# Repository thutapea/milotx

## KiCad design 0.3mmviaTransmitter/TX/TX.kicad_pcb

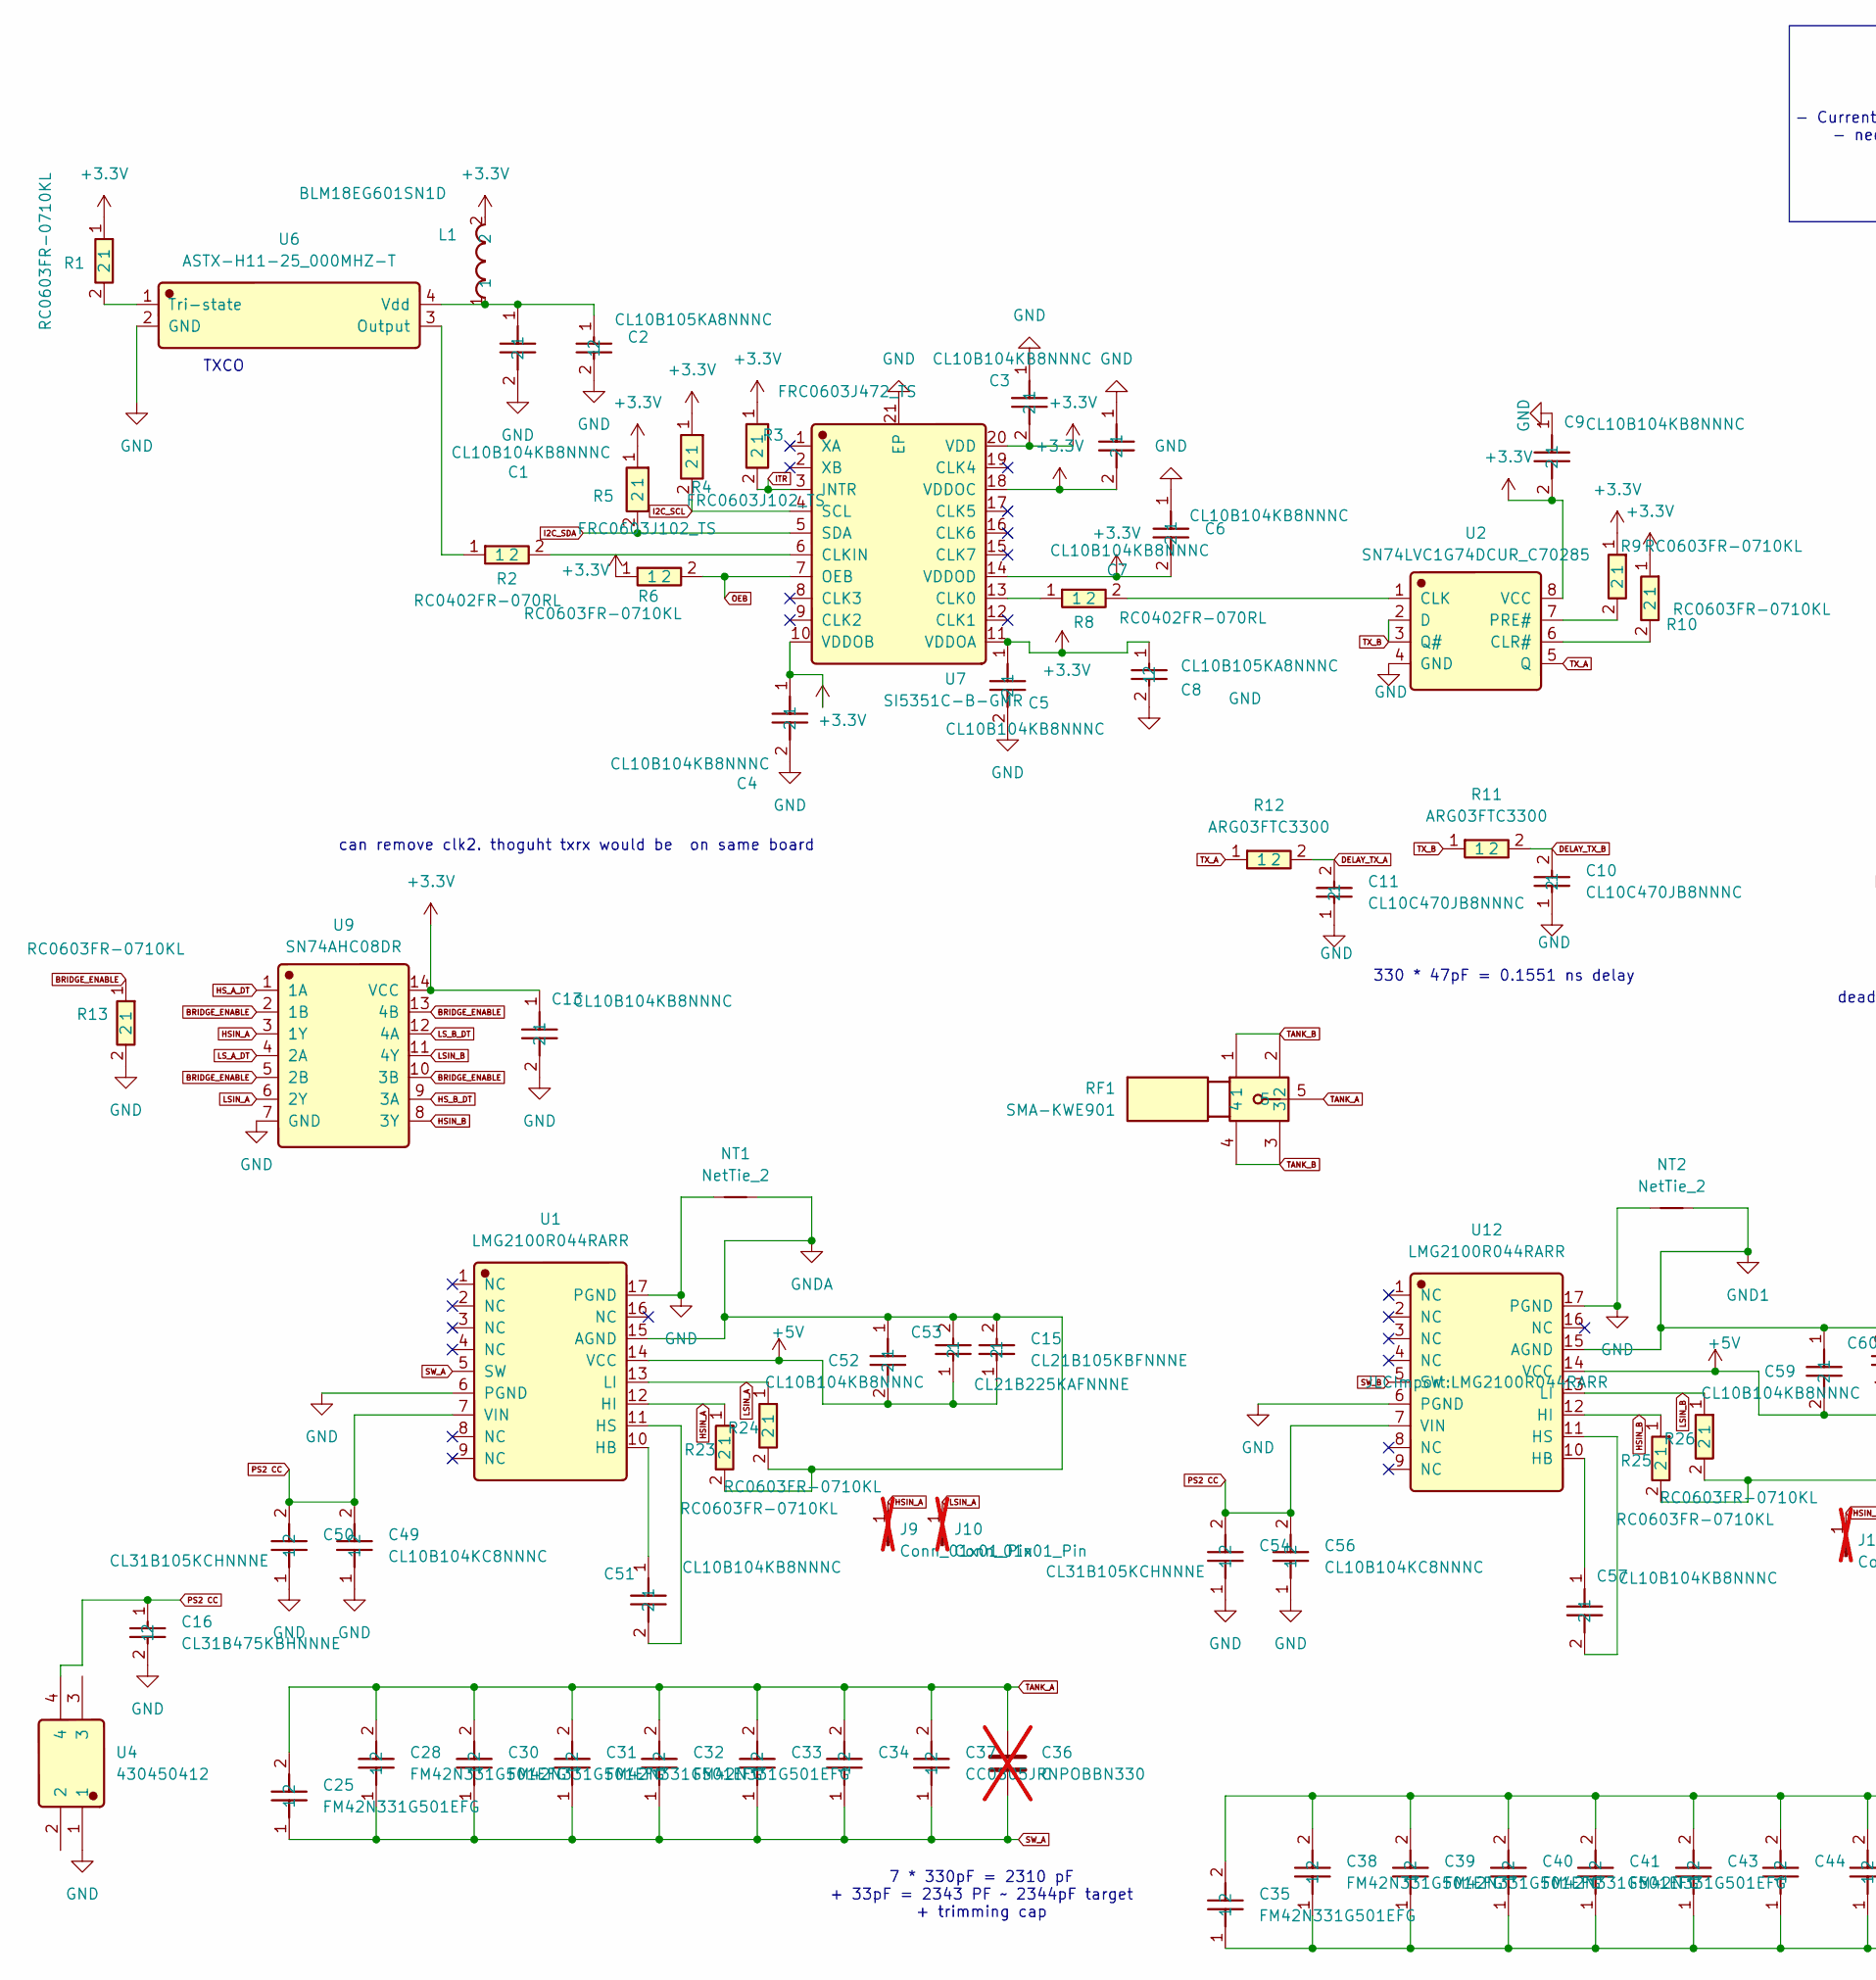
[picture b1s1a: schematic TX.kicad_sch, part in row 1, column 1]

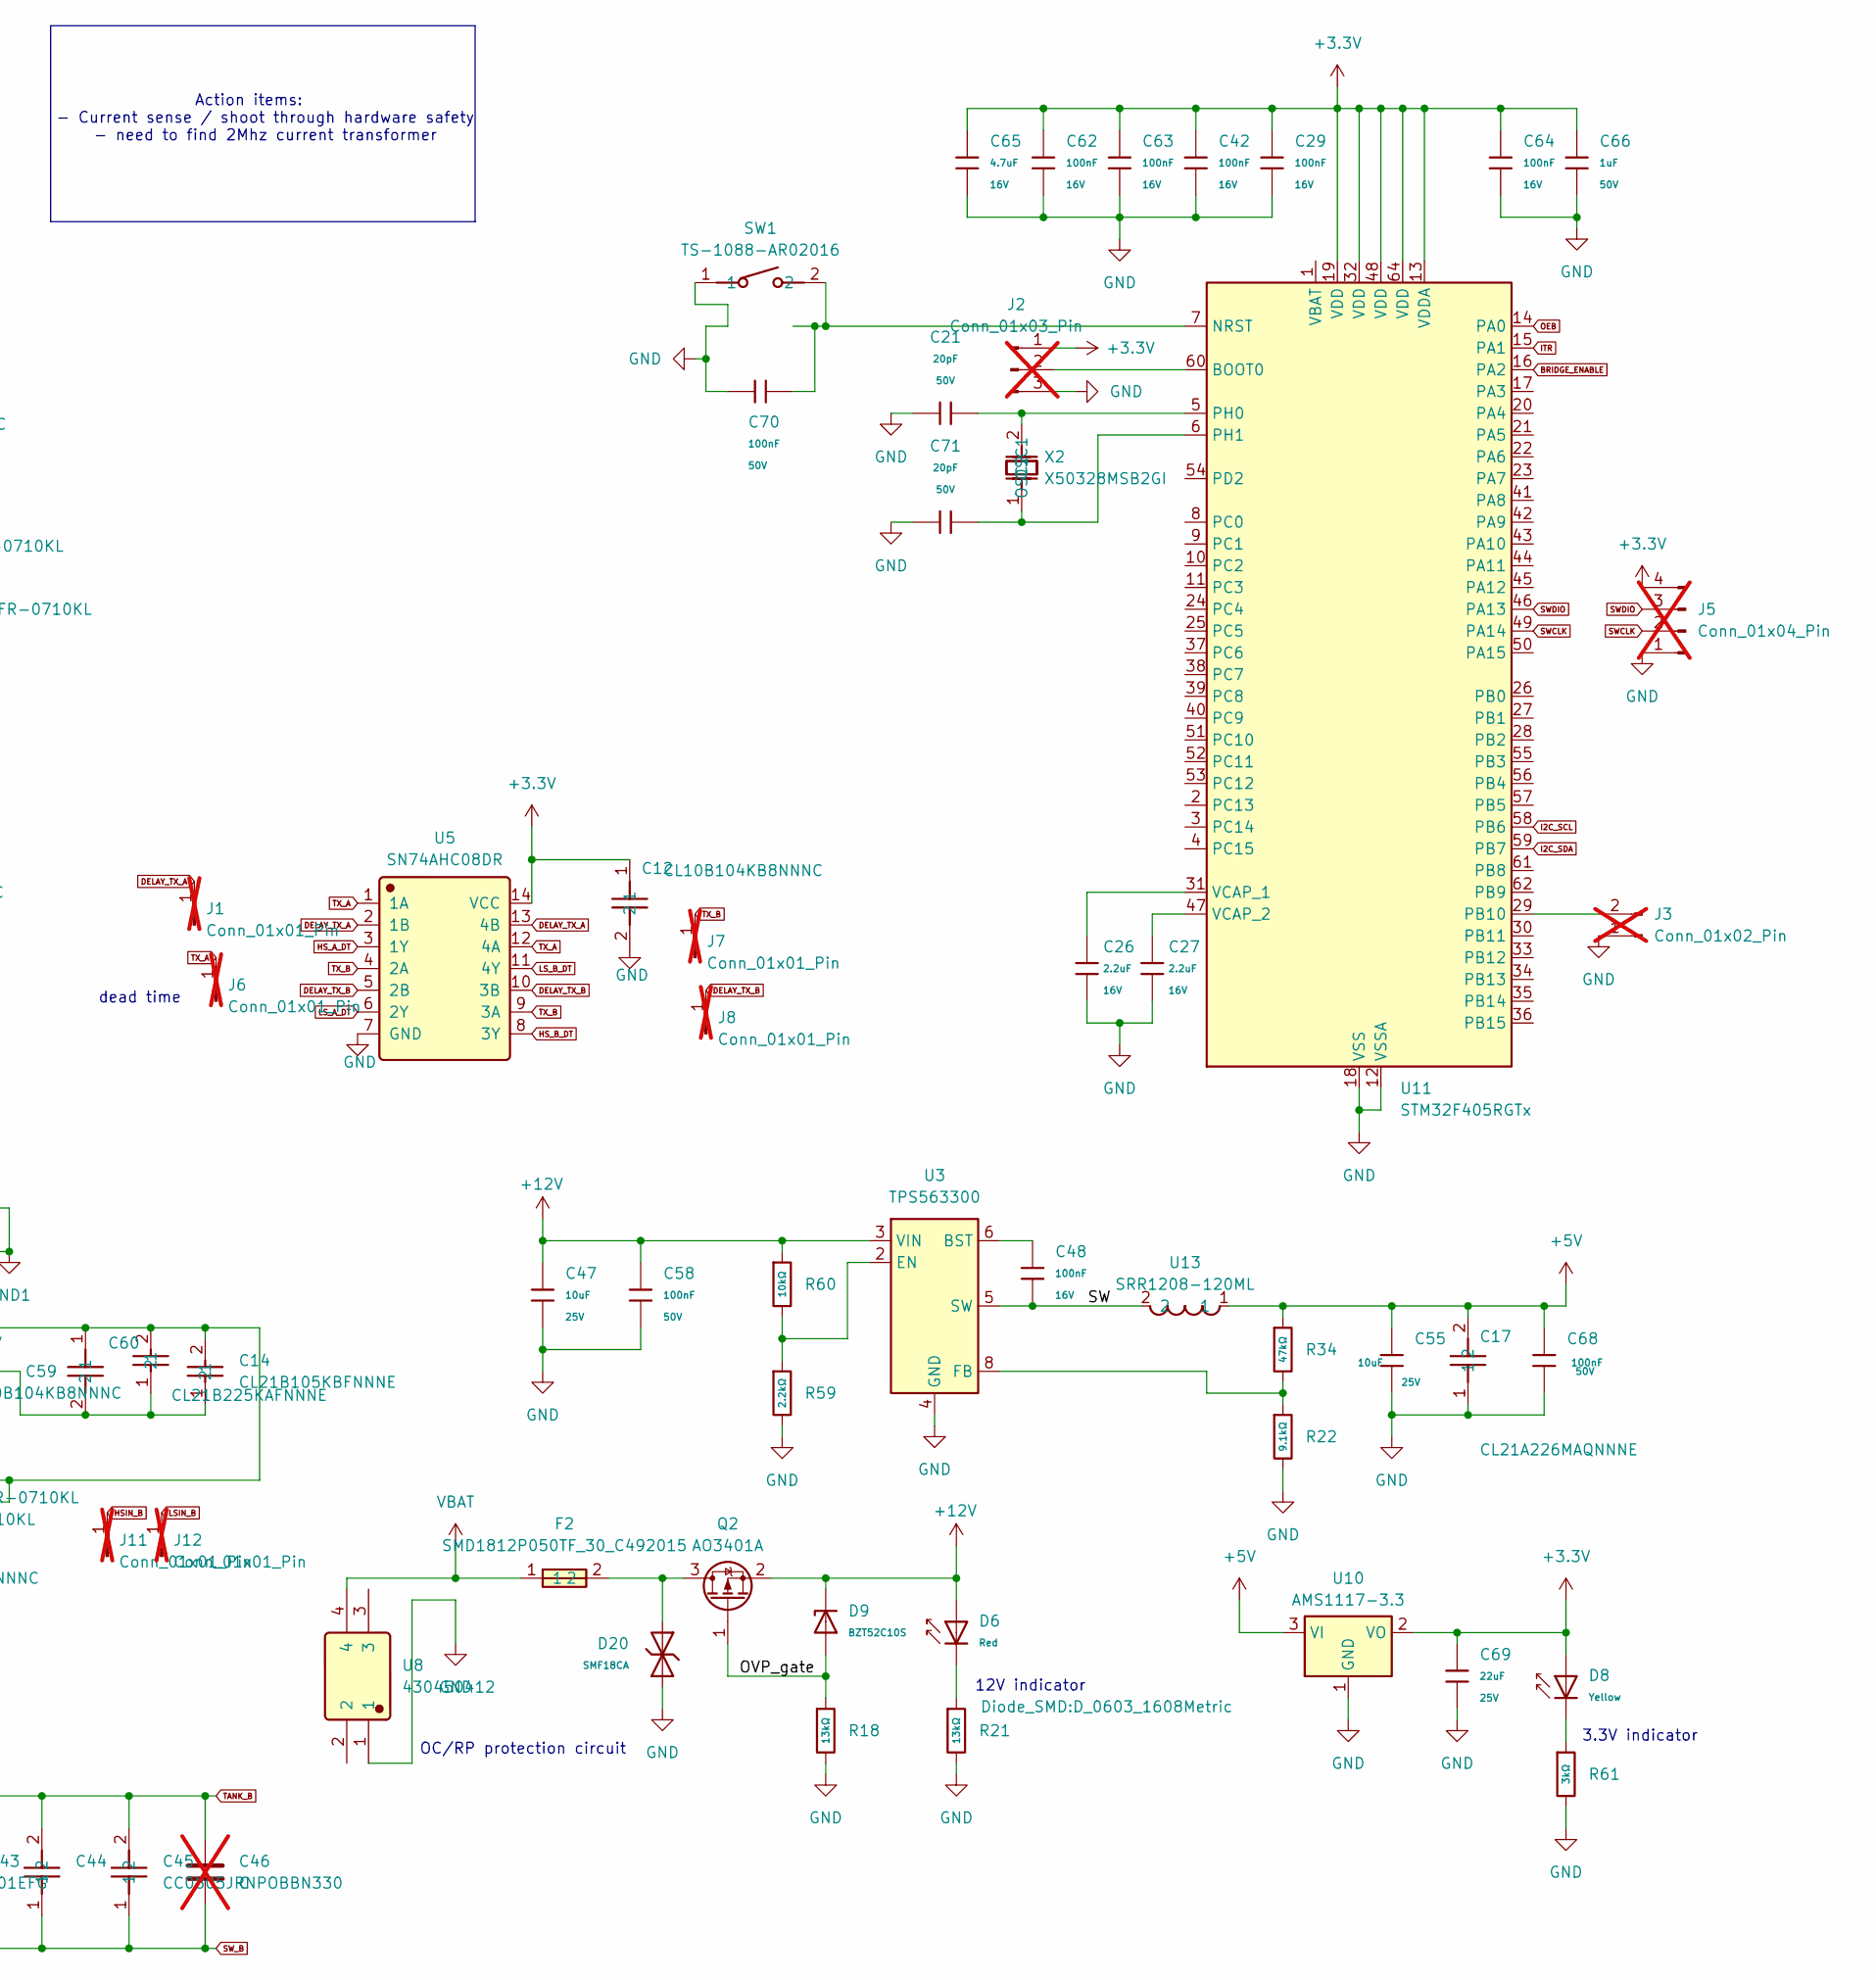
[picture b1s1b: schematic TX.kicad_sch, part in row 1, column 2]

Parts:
C1, C3, C4, C5, C6, C7, C9, C12, C13, C51, C52, C57, C59: CL10B104KB8NNNC; C_0603_1608Metric; Manufacturer Part CL10B104KB8NNNC; LCSC C1591
C2, C8: CL10B105KA8NNNC; C_0603_1608Metric; Manufacturer Part CL10B105KA8NNNC; LCSC C29936
C10, C11: CL10C470JB8NNNC; C_0603_1608Metric; Manufacturer Part CL10C470JB8NNNC; LCSC C1671
C14, C15: CL21B105KBFNNNE; C_0805_2012Metric; Manufacturer Part CL21B105KBFNNNE; LCSC C28323
C16: CL31B475KBHNNNE; C_1206_3216Metric; Manufacturer Part CL31B475KBHNNNE; LCSC C51205
C17: CL21A226MAQNNNE; C_0805_2012Metric; Manufacturer Part CL21A226MAQNNNE; LCSC C45783
C21, C71: 20pF; C_0402_1005Metric; Voltage Rated 50V; Tolerance ±5%; Part 0402CG200J500NT; LCSC C1554
C25, C28, C30, C31, C32, C33, C34, C35, C38, C39, C40, C41, C43, C44: FM42N331G501EFG; C_1808_4520Metric; Manufacturer Part FM42N331G501EFG; LCSC C22376361
C26, C27: 2.2uF; C_0603_1608Metric; Voltage Rated 16V; Tolerance ±10%; Part CL10A225KO8NNNC; LCSC C23630
C29, C42, C48, C62, C63, C64: 100nF; C_0402_1005Metric; Voltage Rated 16V; Tolerance ±10%; Part CL05B104KO5NNNC; LCSC C1525
C36, C46: C; C_0603_1608Metric; not fitted
C37, C45: CC0805JRNPOBBN330; C_0805_2012Metric; Manufacturer Part CC0805JRNPOBBN330; LCSC C113838
C47, C55: 10uF; C_0603_1608Metric; Voltage Rated 25V; Tolerance ±20%; Part CL10A106MA8NRNC; LCSC C96446
C49, C56: CL10B104KC8NNNC; C_0603_1608Metric; Manufacturer Part CL10B104KC8NNNC; LCSC C15725
C50, C54: CL31B105KCHNNNE; C_1206_3216Metric; Manufacturer Part CL31B105KCHNNNE; LCSC C13832
C53, C60: CL21B225KAFNNNE; C_0805_2012Metric; Manufacturer Part CL21B225KAFNNNE; LCSC C19110
C58, C68, C70: 100nF; C_0603_1608Metric; Voltage Rated 50V; Tolerance ±10%; Part CC0603KRX7R9BB104; LCSC C14663
C65: 4.7uF; C_0603_1608Metric; Voltage Rated 16V; Tolerance ±10%; Part CL10A475KO8NNNC; LCSC C19666
C66: 1uF; C_0603_1608Metric; Voltage Rated 50V; Tolerance ±10%; Part CL10A105KB8NNNC; LCSC C15849
C69: 22uF; C_0805_2012Metric; Voltage Rated 25V; Tolerance ±20%; Part CL21A226MAQNNNE; LCSC C45783
D6: Red; D_0603_1608Metric; Part KT-0603R; LCSC C2286
D8: Yellow; D_0603_1608Metric; Forward Voltage (VF) 1.6V~2.6V; Part NCD0603Y2; LCSC C89811
D9: BZT52C10S; D_SOD-323; Part BZT52C10S; LCSC C19077446
D20: SMF18CA; D_SOD-123F; Breakdown Voltage 20V; Part SMF18CA; LCSC C19077513
F2: SMD1812P050TF_30_C492015; Manufacturer Part SMD1812P050TF/30; LCSC C492015
J1, J6, J7, J8, J9, J10, J11, J12: Conn_01x01_Pin; PinHeader_1x01_P2.54mm_Vertical; not fitted
J2: Conn_01x03_Pin; PinSocket_1x03_P2.54mm_Vertical; not fitted
J3: Conn_01x02_Pin; PinHeader_1x02_P2.54mm_Vertical; not fitted
J5: Conn_01x04_Pin; PinHeader_1x04_P2.54mm_Vertical; not fitted
L1: BLM18EG601SN1D; L_0603_1608Metric; Manufacturer Part BLM18EG601SN1D; LCSC C20345
NT1, NT2: NetTie_2; NetTie-2_SMD_Pad2.0mm
Q2: AO3401A; SOT-23
R1, R6, R9, R10, R13, R23, R24, R25, R26: RC0603FR-0710KL; R_0603_1608Metric; Manufacturer Part RC0603FR-0710KL; LCSC C98220
R2, R8: RC0402FR-070RL; R_0402_1005Metric; Manufacturer Part RC0402FR-070RL; LCSC C106231
R3: FRC0603J472_TS; R_0603_1608Metric; Manufacturer Part FRC0603J472 TS; LCSC C2907166
R4, R5: FRC0603J102_TS; R_0603_1608Metric; Manufacturer Part FRC0603J102 TS; LCSC C2907113
R11, R12: ARG03FTC3300; R_0603_1608Metric; Manufacturer Part ARG03FTC3300; LCSC C217969
R18, R21: 13kΩ; R_0603_1608Metric; Overload Voltage (Max) 75V; Tolerance ±1%; Part 0603WAF1302T5E; LCSC C22797
R22: 9.1kΩ; R_0603_1608Metric; Overload Voltage (Max) 75V; Tolerance ±1%; Part 0603WAF9101T5E; LCSC C23260
R34: 47kΩ; R_0402_1005Metric; Overload Voltage (Max) 50V; Tolerance ±1%; Part 0402WGF4702TCE; LCSC C25792
R59: 2.2kΩ; R_0402_1005Metric; Overload Voltage (Max) 50V; Tolerance ±1%; Part 0402WGF2201TCE; LCSC C25879
R60: 10kΩ; R_0402_1005Metric; Overload Voltage (Max) 50V; Tolerance ±1%; Part 0402WGF1002TCE; LCSC C25744
R61: 3kΩ; R_0603_1608Metric; Overload Voltage (Max) 75V; Tolerance ±1%; Part 0603WAF3001T5E; LCSC C4211
RF1: SMA-KWE901; Manufacturer Part SMA-KWE901; LCSC C914553
SW1: TS-1088-AR02016; SW_PUSH_1P1T_6x3.5mm_H5.0_APEM_MJTP1250; Manufacturer Part TS-1088-AR02016; LCSC C54141293
U1, U12: LMG2100R044RARR; Manufacturer Part LMG2100R044RARR; LCSC C22453052
U2: SN74LVC1G74DCUR_C70285; VSSOP-8_2.3x2mm_P0.5mm; Manufacturer Part SN74LVC1G74DCUR; LCSC C70285
U3: TPS563300; SOT-583-8
U4, U8: 430450412; Molex_Micro-Fit_3.0_43045-0412_2x02_P3.00mm_Vertical; Manufacturer Part 430450412; LCSC C277721
U5, U9: SN74AHC08DR; SOIC-14_3.9x8.7mm_P1.27mm; Manufacturer Part SN74AHC08DR; LCSC C6937
U6: ASTX-H11-25_000MHZ-T; Crystal_SMD_3225-4Pin_3.2x2.5mm; Manufacturer Part ASTX-H11-25.000MHZ-T; LCSC C7217716
U7: SI5351C-B-GMR; Manufacturer Part SI5351C-B-GMR; LCSC C2649375
U10: AMS1117-3.3; SOT-223-3_TabPin2
U11: STM32F405RGTx; LQFP-64_10x10mm_P0.5mm; LCSC C15742
U13: SRR1208-120ML; Manufacturer Part SRR1208-120ML; LCSC C1329356
X2: X50328MSB2GI; Crystal_SMD_5032-2Pin_5.0x3.2mm; Manufacturer Part X50328MSB2GI; LCSC C115962

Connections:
+3.3V: C3.2, C4.1, C5.1, C6.2, C7.2, C8.1, C9.2, C12.1, C13.1, C29.1, C42.1, C62.1, C63.1, C64.1, C65.1, C66.1, C69.1, D8.2, J2.1, J5.4, L1.2, R1.1, R3.1, R4.1, R5.1, R6.1, R9.1, R10.1, U2.8 (VCC), U5.14 (VCC), U7.10 (VDDOB), U7.11 (VDDOA), U7.14 (VDDOD), U7.18 (VDDOC), U7.20 (VDD), U9.14 (VCC), U10.2 (VO), U11.13 (VDDA), U11.19 (VDD), U11.32 (VDD), U11.48 (VDD), U11.64 (VDD); also elsewhere on the board
+5V: C14.1, C15.1, C17.2, C52.2, C53.1, C55.1, C59.2, C60.1, C68.1, R34.1, U1.14 (VCC), U10.3 (VI), U12.14 (VCC), U13.1
+12V: C47.1, C58.1, D6.2, D9.1, Q2.2 (S), R60.1, U3.3 (VIN); also elsewhere on the board
/OVP_gate: D9.2, Q2.1 (G), R18.1
/SW: C48.2, U3.5 (SW), U13.2
BRIDGE_ENABLE: R13.1, U9.2 (1B), U9.5 (2B), U9.10 (3B), U9.13 (4B), U11.16 (PA2)
DELAY_TX_A: C11.2, J1.1 (Pin_1_1), R12.2, U5.2 (1B), U5.13 (4B)
DELAY_TX_B: C10.2, J8.1 (Pin_1_1), R11.2, U5.5 (2B), U5.10 (3B)
GND: C1.2, C2.2, C3.1, C4.2, C5.2, C6.1, C7.1, C8.2, C9.1, C10.1, C11.1, C12.2, C13.2, C16.2, C17.1, C21.1, C26.2, C27.2, C29.2, C42.2, C47.2, C49.1, C50.1, C54.1, C55.2, C56.1, C58.2, C62.2, C63.2, C64.2, C65.2, C66.2, C68.2, C69.2, C70.2, C71.1, D20.1, J2.3, J3.1, J5.1, NT1.1, NT2.1, R13.2, R18.2, R21.2, R22.2, R59.2, R61.2, SW1.1, U1.6 (PGND), U1.17 (PGND), U2.4 (GND), U3.4 (GND), U4.1, U5.7 (GND), U6.2 (GND), U7.21 (EP), U8.1, U9.7 (GND), U10.1 (GND), U11.12 (VSSA), U11.18 (VSS), U11.63 (VSS), U12.6 (PGND), U12.17 (PGND)
GND1: C14.2, C59.1, C60.2, NT2.2, R25.2, R26.2, U12.15 (AGND)
GNDA: C15.2, C52.1, C53.2, NT1.2, R23.2, R24.2, U1.15 (AGND)
HSIN_A: J9.1 (Pin_1_1), R23.1, U1.12 (HI), U9.3 (1Y)
HSIN_B: J11.1 (Pin_1_1), R25.1, U9.8 (3Y), U12.12 (HI)
HS_A_DT: U5.3 (1Y), U9.1 (1A)
HS_B_DT: U5.8 (3Y), U9.9 (3A)
I2C_SCL: R4.2, U7.4 (SCL), U11.58 (PB6)
I2C_SDA: R5.2, U7.5 (SDA), U11.59 (PB7)
ITR: R3.2, U7.3 (INTR), U11.15 (PA1)
LSIN_A: J10.1 (Pin_1_1), R24.1, U1.13 (LI), U9.6 (2Y)
LSIN_B: J12.1 (Pin_1_1), R26.1, U9.11 (4Y), U12.13 (LI)
LS_A_DT: U5.6 (2Y), U9.4 (2A)
LS_B_DT: U5.11 (4Y), U9.12 (4A)
unnamed: D6.1, R21.1
unnamed: D8.1, R61.1
unnamed: J2.2, U11.60 (BOOT0)
unnamed: J3.2, U11.29 (PB10)
unnamed: D20.2, F2.2, Q2.3 (D)
unnamed: C51.1, U1.10 (HB)
unnamed: C51.2, U1.11 (HS)
unnamed: R8.2, U2.1 (CLK)
unnamed: R9.2, U2.6 (CLR#)
unnamed: R10.2, U2.7 (PRE#)
unnamed: C48.1, U3.6 (BST)
unnamed: R59.1, R60.2, U3.2 (EN)
unnamed 34: R22.1, R34.2, U3.8 (FB); also elsewhere on the board
unnamed: R2.1, U6.3 (Output)
unnamed: R1.2, U6.1 (Tri-state)
unnamed: C1.1, C2.1, L1.1, U6.4 (Vdd)
unnamed: R8.1, U7.13 (CLK0)
unnamed: R2.2, U7.6 (CLKIN)
unnamed: C70.1, SW1.2, U11.7 (NRST)
unnamed: C21.2, U11.5 (PH0), X2.2 (OSC2)
unnamed: C71.2, U11.6 (PH1), X2.1 (OSC1)
unnamed: C26.1, U11.31 (VCAP_1)
unnamed: C27.1, U11.47 (VCAP_2)
unnamed: C57.1, U12.10 (HB)
unnamed: C57.2, U12.11 (HS)
OEB: R6.2, U7.7 (OEB), U11.14 (PA0)
PS2 CC: C16.1, C49.2, C50.2, C54.2, C56.2, U1.7 (VIN), U4.4, U12.7 (VIN)
SWCLK: J5.2, U11.49 (PA14)
SWDIO: J5.3, U11.46 (PA13)
SW_A: C25.1, C28.1, C30.1, C31.1, C32.1, C33.1, C34.1, C36.2, C37.1, U1.5 (SW)
SW_B: C35.1, C38.1, C39.1, C40.1, C41.1, C43.1, C44.1, C45.1, C46.2, U12.5 (SW)
TANK_A: C25.2, C28.2, C30.2, C31.2, C32.2, C33.2, C34.2, C36.1, C37.2, RF1.5
TANK_B: C35.2, C38.2, C39.2, C40.2, C41.2, C43.2, C44.2, C45.2, C46.1, RF1.1, RF1.2, RF1.3, RF1.4
TX_A: J6.1 (Pin_1_1), R12.1, U2.5 (Q), U5.1 (1A), U5.12 (4A)
TX_B: J7.1 (Pin_1_1), R11.1, U2.2 (D), U2.3 (Q#), U5.4 (2A), U5.9 (3A)
VBAT: F2.1, U8.4

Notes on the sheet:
TXCO
Action items: - Current sense / shoot through hardware safety - need to find 2Mhz current transformer
7 * 330pF = 2310 pF + 33pF = 2343 PF ~ 2344pF target + trimming cap
330 * 47pF = 0.1551 ns delay
12V indicator
OC/RP protection circuit
dead time
can remove clk2. thoguht txrx would be on same board
3.3V indicator

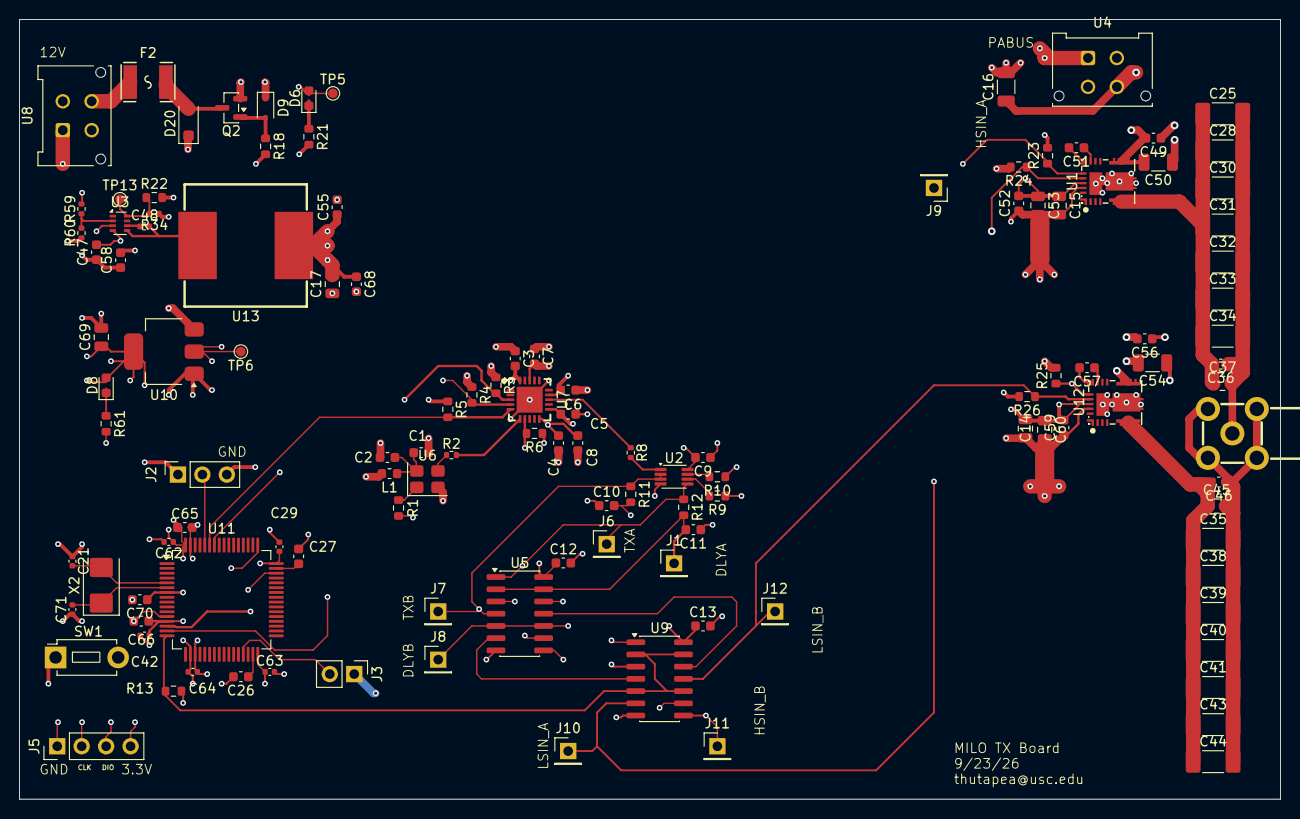
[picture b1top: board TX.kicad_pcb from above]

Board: 6 copper layers, 131.0 x 81.0 mm, 125 parts (0 on the bottom side), 58 nets.

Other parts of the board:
TP5, TP6, TP13: TestPoint_Small; TestPoint_Pad_D1.0mm

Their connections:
+3.3V: TP6.1 (1_1); also elsewhere on the board
+12V: TP5.1 (1_1); also elsewhere on the board
unnamed 34: TP13.1 (1_1); also elsewhere on the board

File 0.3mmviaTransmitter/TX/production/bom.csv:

Designator,Footprint,Quantity,Value,LCSC Part #
"C1, C12, C13, C3, C4, C5, C51, C52, C57, C59, C6, C7, C9",0603,13,CL10B104KB8NNNC,C1591
"C10, C11",0603,2,CL10C470JB8NNNC,C1671
"C14, C15",0805,2,CL21B105KBFNNNE,C28323
C16,1206,1,CL31B475KBHNNNE,C51205
C17,0805,1,CL21A226MAQNNNE,C45783
"C2, C8",0603,2,CL10B105KA8NNNC,C29936
"C21, C71",0402,2,20pF,C1554
"C25, C28, C30, C31, C32, C33, C34, C35, C38, C39, C40, C41, C43, C44",1808,14,FM42N331G501EFG,C22376361
"C26, C27",0603,2,2.2uF,C23630
"C29, C42, C48, C62, C63, C64",0402,6,100nF,C1525
"C37, C45",0805,2,CC0805JRNPOBBN330,C113838
"C47, C55",0603,2,10uF,C96446
"C49, C56",0603,2,CL10B104KC8NNNC,C15725
"C50, C54",1206,2,CL31B105KCHNNNE,C13832
"C53, C60",0805,2,CL21B225KAFNNNE,C19110
"C58, C68, C70",0603,3,100nF,C14663
C65,0603,1,4.7uF,C19666
C66,0603,1,1uF,C15849
C69,0805,1,22uF,C45783
D20,D_SOD-123F,1,SMF18CA,C19077513
D6,0603,1,Red,C2286
D8,0603,1,Yellow,C89811
D9,D_SOD-323,1,BZT52C10S,C19077446
F2,SMD1812P050TF_30_C492015,1,SMD1812P050TF_30_C492015,C492015
L1,0603,1,BLM18EG601SN1D,C20345
Q2,SOT-23,1,AO3401A,
"R1, R10, R13, R23, R24, R25, R26, R6, R9",0603,9,RC0603FR-0710KL,C98220
"R11, R12",0603,2,ARG03FTC3300,C217969
"R18, R21",0603,2,13kΩ,C22797
"R2, R8",0402,2,RC0402FR-070RL,C106231
R22,0603,1,9.1kΩ,C23260
R3,0603,1,FRC0603J472_TS,C2907166
R34,0402,1,47kΩ,C25792
"R4, R5",0603,2,FRC0603J102_TS,C2907113
R59,0402,1,2.2kΩ,C25879
R60,0402,1,10kΩ,C25744
R61,0603,1,3kΩ,C4211
RF1,SMA-KWE901,1,SMA-KWE901,C914553
SW1,SW_PUSH_1P1T_6x3.5mm_H5.0_APEM_MJTP1250,1,TS-1088-AR02016,C54141293
"U1, U12",LMG2100R044RARR,2,LMG2100R044RARR,C22453052
U10,SOT-223-3_TabPin2,1,AMS1117-3.3,
U11,LQFP-64_10x10mm_P0.5mm,1,STM32F405RGTx,C15742
U13,SRR1208-120ML,1,SRR1208-120ML,C1329356
U2,VSSOP-8_2.3x2mm_P0.5mm,1,SN74LVC1G74DCUR_C70285,C70285
U3,SOT-583-8,1,TPS563300,
"U4, U8",Molex_Micro-Fit_3.0_43045-0412_2x02_P3.00mm_Vertical,2,430450412,C277721
"U5, U9",SOIC-14_3.9x8.7mm_P1.27mm,2,SN74AHC08DR,C6937
U6,Crystal_SMD_3225-4Pin_3.2x2.5mm,1,ASTX-H11-25_000MHZ-T,C7217716
U7,SI5351C-B-GMR,1,SI5351C-B-GMR,C2649375
X2,Crystal_SMD_5032-2Pin_5.0x3.2mm,1,X50328MSB2GI,C115962

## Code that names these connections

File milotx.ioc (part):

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Mcu.Name=STM32F405RGTx
Mcu.Package=LQFP64
Mcu.UserName=STM32F405RGTx
PA0-WKUP.Signal=GPIO_Output
PA13.Mode=Serial_Wire
PA13.Signal=SYS_JTMS-SWDIO
PA14.Mode=Serial_Wire
PA14.Signal=SYS_JTCK-SWCLK
PB10.Mode=Half_duplex(single_wire_mode)
PB10.Signal=USART3_TX
PB6.Mode=I2C
PB6.Signal=I2C1_SCL
PB7.Mode=I2C
PB7.Signal=I2C1_SDA
PH0-OSC_IN.Mode=HSE-External-Oscillator
PH0-OSC_IN.Signal=RCC_OSC_IN
PH1-OSC_OUT.Mode=HSE-External-Oscillator
PH1-OSC_OUT.Signal=RCC_OSC_OUT
RCC.HSE_VALUE=8000000
RCC.SYSCLKFreq_VALUE=168000000
RCC.SYSCLKSource=RCC_SYSCLKSOURCE_PLLCLK
board=custom
